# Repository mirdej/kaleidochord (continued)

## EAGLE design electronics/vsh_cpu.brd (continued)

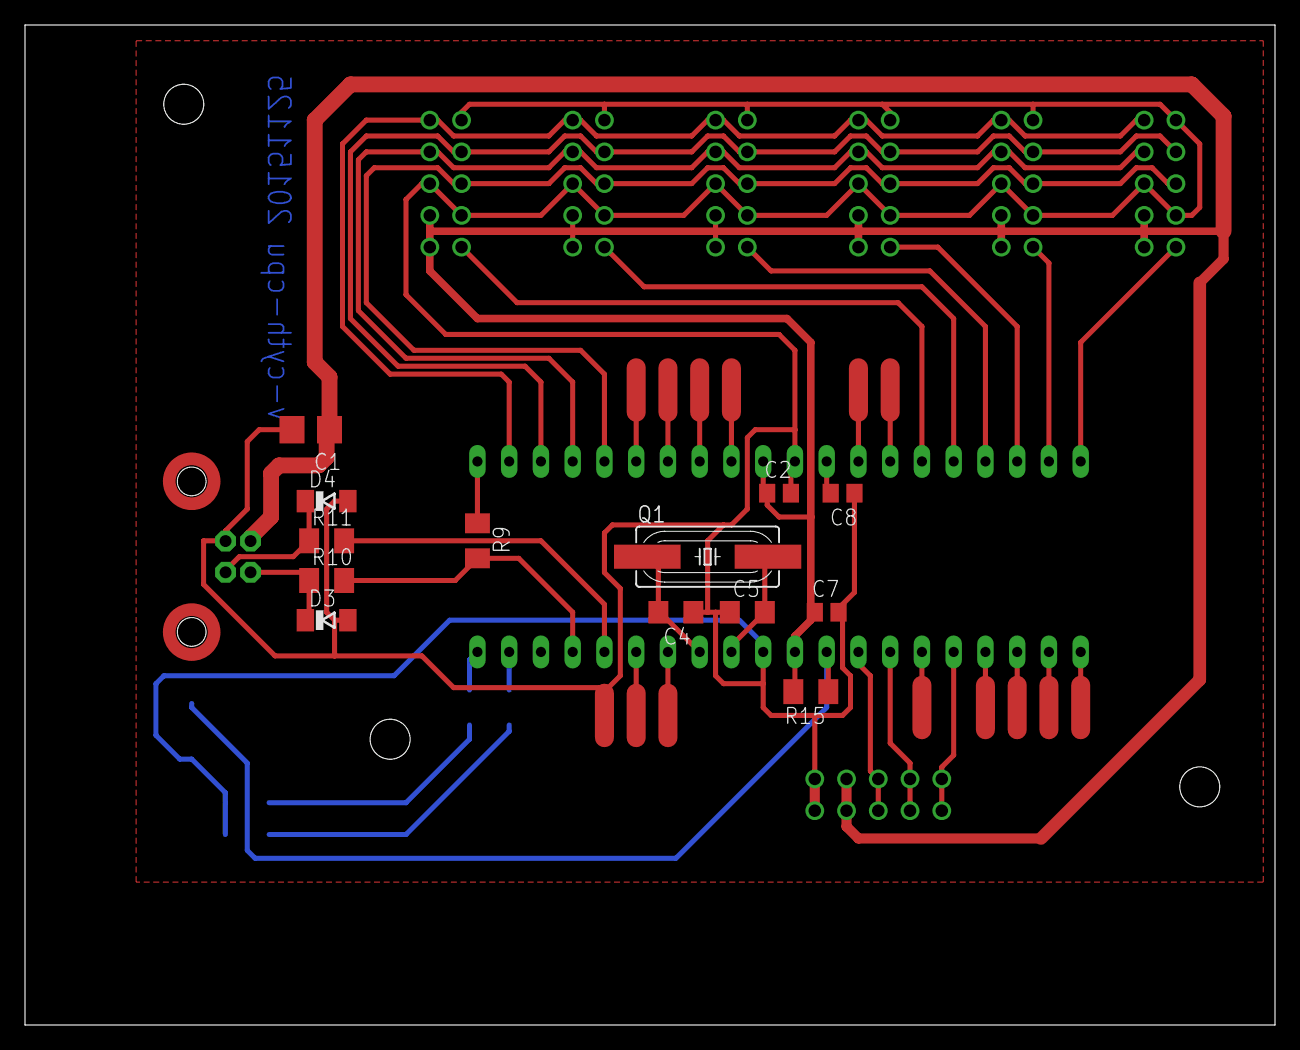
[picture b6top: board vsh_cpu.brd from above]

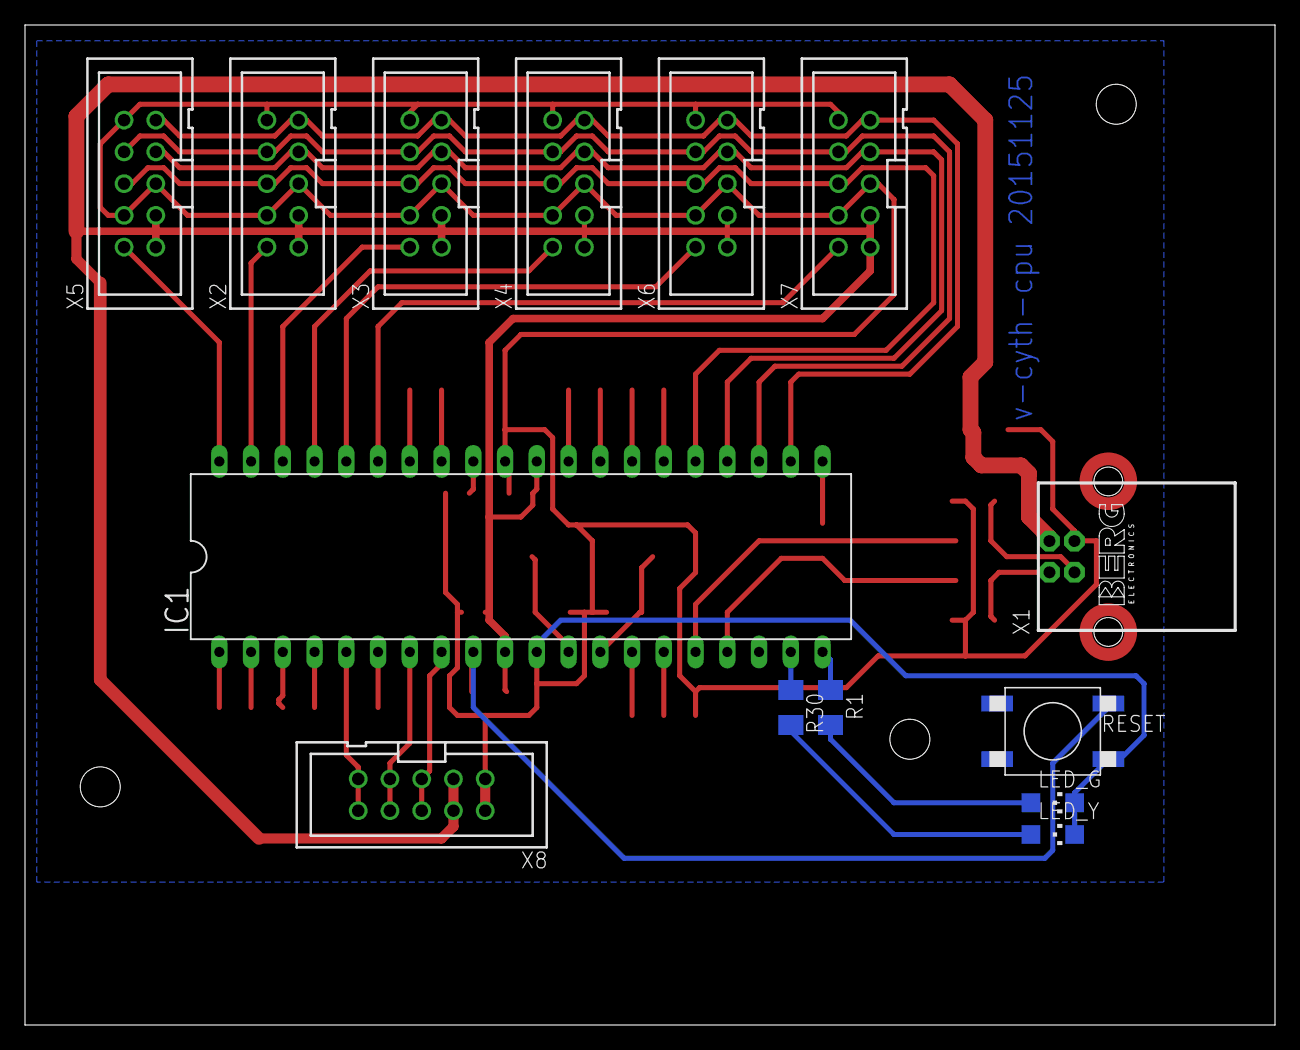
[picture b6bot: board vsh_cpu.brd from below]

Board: 2 copper layers, 100.0 x 80.0 mm, 32 parts (14 on the bottom side), 41 nets.

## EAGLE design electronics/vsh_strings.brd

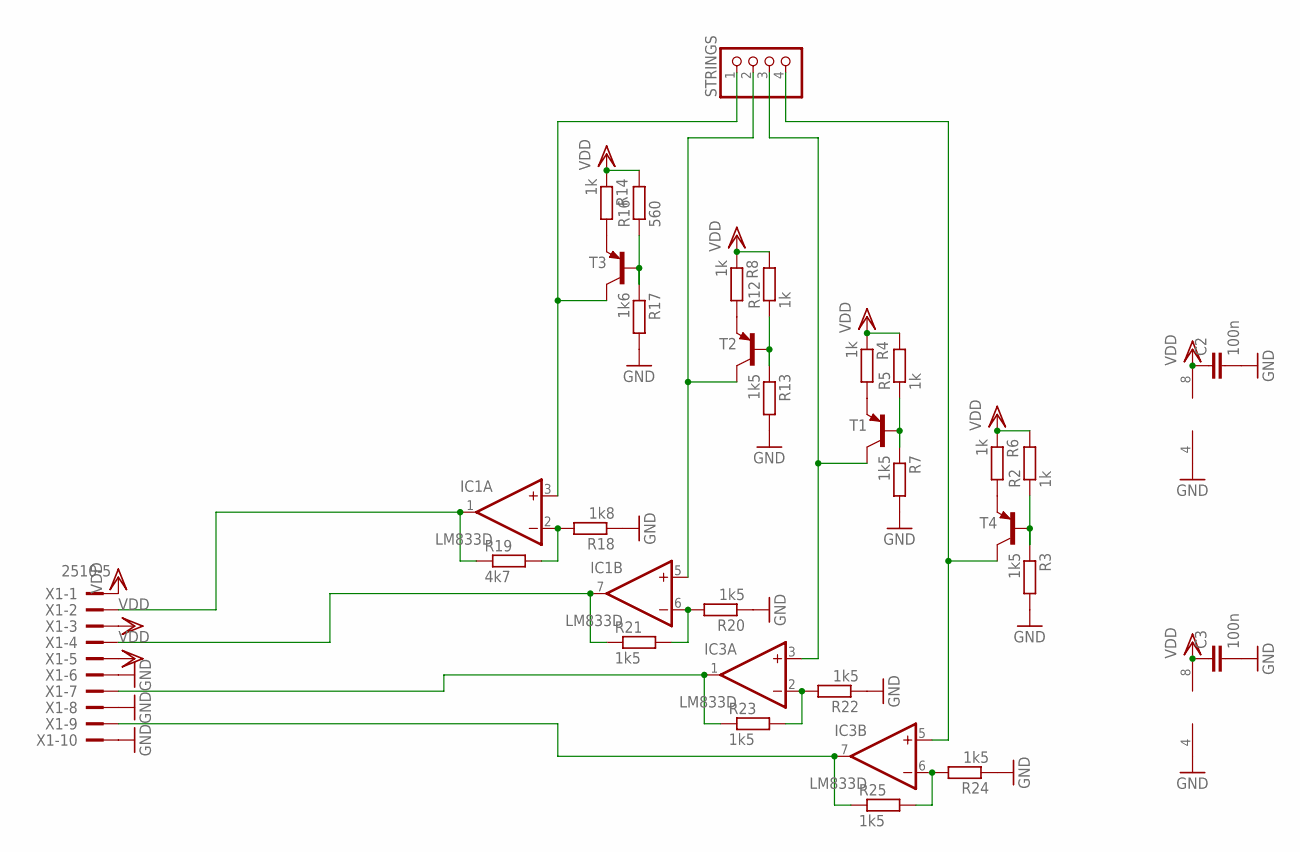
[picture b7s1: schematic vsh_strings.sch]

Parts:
C2, C3: 100n; C0603
IC1, IC3: LM833D; SO08
R2, R4, R5, R6, R8, R12, R14: 1k; R1206
R3, R7, R13, R20, R21, R22, R23, R24, R25: 1k5; R1206
R16: 560; R1206
R17: 1k6; R1206
R18: 1k8; R1206
R19: 4k7; R1206
STRINGS: PINHD-1X4; 1X04
T1, T2, T3, T4: -PNP-SOT23-BCE; SOT23-BCE
X1: 2510-5; PAK100/2500-5-10

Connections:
GND: C2.2, C3.2, IC1.4 (V-), IC3.4 (V-), R3.2, R7.2, R13.2, R17.2, R18.1, R20.1, R22.1, R24.1, X1.6, X1.8, X1.10
unnamed: IC1.1 (OUT), R19.1, X1.2
unnamed: IC1.2 (-IN), R18.2, R19.2
unnamed: IC1.6 (-IN), R20.2, R21.2
unnamed: R6.2, T4.E
unnamed: IC3.5 (+IN), STRINGS.4, T4.C
unnamed: R2.1, R3.1, T4.B
unnamed: R4.2, T1.E
unnamed: IC3.3 (+IN), STRINGS.3, T1.C
unnamed: R5.1, R7.1, T1.B
unnamed: R8.2, T2.E
unnamed: IC1.5 (+IN), STRINGS.2, T2.C
unnamed: R12.1, R13.1, T2.B
unnamed: R14.2, T3.E
unnamed: IC1.3 (+IN), STRINGS.1, T3.C
unnamed: R16.1, R17.1, T3.B
unnamed: IC1.7 (OUT), R21.1, X1.4
unnamed: IC3.2 (-IN), R22.2, R23.2
unnamed: IC3.6 (-IN), R24.2, R25.2
unnamed: IC3.1 (OUT), R23.1, X1.7
unnamed: IC3.7 (OUT), R25.1, X1.9
VDD: C2.1, C3.1, IC1.8 (V+), IC3.8 (V+), R2.2, R4.1, R5.2, R6.1, R8.1, R12.2, R14.1, R16.2, X1.1, X1.3, X1.5

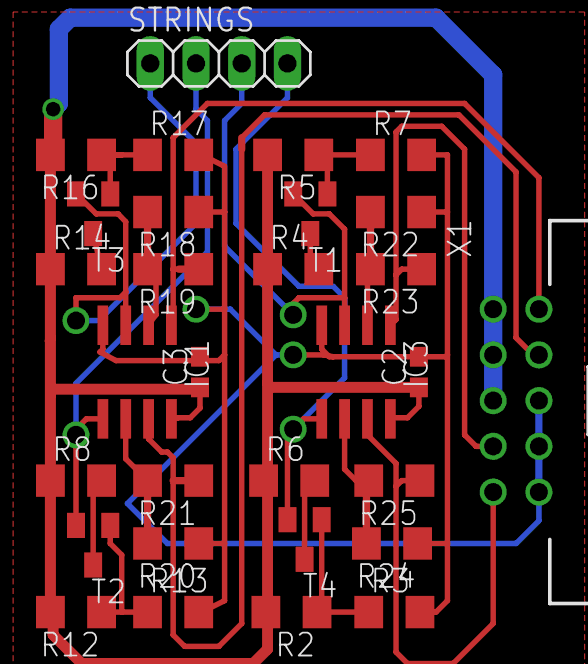
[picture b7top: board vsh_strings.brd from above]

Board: 2 copper layers, 30 parts (0 on the bottom side), 22 nets.

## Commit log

2015-12-05 initial import. hardware and firmware
2015-12-05 using timer library
2015-12-06 add force sending
2015-12-06 four videobass-like layers with eq lumakey untested
2015-12-07 4 vb layers working more or less correctly incl keying and flipping
2015-12-07 added not-messages when string is pressed/released
2015-12-08 bugfix strings won't work after force send
2015-12-08 sends mixer + solo buttons
2015-12-08 vcam works
2015-12-08 cam working
2015-12-09 incl sketcher
2015-12-09 feedback blur, delay and correct size. basic visualkitchen functionality is here
2015-12-09 renamed files to reflect loading order
2015-12-09 add and adapted 3screenprojector from visualkitchen
2015-12-10 add untested recordable control in
2015-12-10 add mode 0 to dial painter
2015-12-10 bugfix controller 0
2015-12-10 with control-animation recording
2015-12-13 live input. simple projector
2015-12-13 performance improvement by copying eq_texture to strip. integrateed vcam deamon. hi.tools 1.0.3 doesnt seem to crash
2015-12-13 recording indicator
2015-12-17 add modifyable private copy of GnusbuinoMIDI library. tried to increase buffer size, removed redudancy check, to try to prevent hangups
2016-01-09 renamed project
2016-07-27 hack to fix midi issues (?)
2016-08-04 chaning author
2016-08-04 add onecopy to allpatchers
2016-08-04 remove preview screen
2016-08-04 better track automation recording?
2016-08-04 tap to reset beat counter
2016-08-04 add master level of output before feedback
2016-08-04 add audio sync and MIDI rt in
2016-08-04 tryout to make channel respond to music. slows dwon to 13fps
2016-08-09 new midi syny.version horizon liquide repetition mardi.
2016-08-10 renamed UI patch
2016-08-10 seperate engine completely from UI to be able to run on separate computers connected through network
2016-08-10 UI side of separated system
2016-08-10 rename engine
2016-08-10 auto fullscreen and hide cursor
2016-08-10 fixed movie path isssue. whatismyip does not tell 127.51.. adresses
2016-08-10 fixed flipped movie output
2016-08-10 3 channel audio input with filter
2016-08-10 string does not move with sound in videobass mode.
2016-08-10 resolve conflict with fb_blur ctrl. add attack & decay
2016-08-17 version schaffhausen
2016-08-27 preference for window position and menu visibility
2016-08-27 integrate vcam handling
2016-08-27 remember menubar setting
2016-08-27 add send/receive connected indicators
2016-08-27 fixed window scroll
2016-09-09 version reine berthe with audio analyzer
2016-09-09 add circle proj
2016-09-10 ui in presentation mode. trying to add live recording funtionality for gestes ephemeres
2016-09-11 automatically mount melchior
2016-09-11 small cleanup. print fimstrip messages
2016-09-11 structured and verbose connection on init
2016-09-11 correct filepaths for clips/movies/recordings. playing back recordings works
2016-09-11 fix bug with gl.text2d
2016-09-11 connect live rec pedal. only connect to network if my ip is right
2016-09-11 fix recording path to filmstrip. add vb-has-live communication
2016-09-11 load settings on load ;-)
2016-09-12 before changing ui resolution
2016-09-12 change ui resolution to 1280 720
2016-09-12 send vb_has_videoinput every 20s
2016-09-17 add control for gestes illumination background
2016-09-19 version for canceled gestes ephemeres concert
2016-09-19 changed string calibration to two phase proprocess: first set all lows, then all hights
2016-09-19 cosmetics
2016-09-19 adding pattr system for presets and chnnel swapping. first attempt at channel swap
2016-09-20 cleanup ui channel behind scenes
2016-09-20 better button handling. unfolding?
2016-09-20 new trigger logic
2016-09-20 prevent volume change when keeping finger on string afterselcting a clip
2016-09-20 prevent release of string to still change level$
2016-09-20 remove unused mode button from picture
2016-09-20 removed unused trigger and fld btns from lanes 5-7, suppressed clip out of range m,essage at startup
2016-09-20 add pattrstorage interface
2016-09-21 first version with sync-track-to-beat
2016-09-21 synced player was not being banged
2016-09-21 cosmetic cleanup
2016-09-24 swapping and loading new clips sometimes fail. trying to figure out why
2016-09-24 trigger was simple bang, not 1-0. initial unfold 0
2016-09-24 seems to have fixerd problems at least a bit. remove debug messages
2016-09-24 add ui brightness controls
2017-01-06 remove pattrstorage-interface for now
2017-01-06 add ca 10sec Live video delay. try to fix 'speed change deops frame rate' problem
2017-01-06 add live-mode and scrub buttons back
2017-01-06 change gnusb to gnusb#2 because of e weird bug
2017-02-06 change grab engine to avf because blackmagic. fabienne. add screenmix controls back to zither
2017-02-06 fix gnusb name ghetto for audio analizer
2017-03-31 version for TURNOUT
2017-03-31 try to fix changing midi device names
2017-03-31 add missing abstractions for previous commit
2017-03-31 close subpatcher. fix ctlin
2017-04-19 let zither send on midi channel 13
2017-04-19 zither masp patch only listens on midi channel 13
2017-04-19 fix many ctlins folow others
2017-04-19 listen for pedal only on midi channel 11. completely got rid of name based midi controller matching as this seems broken in max7
